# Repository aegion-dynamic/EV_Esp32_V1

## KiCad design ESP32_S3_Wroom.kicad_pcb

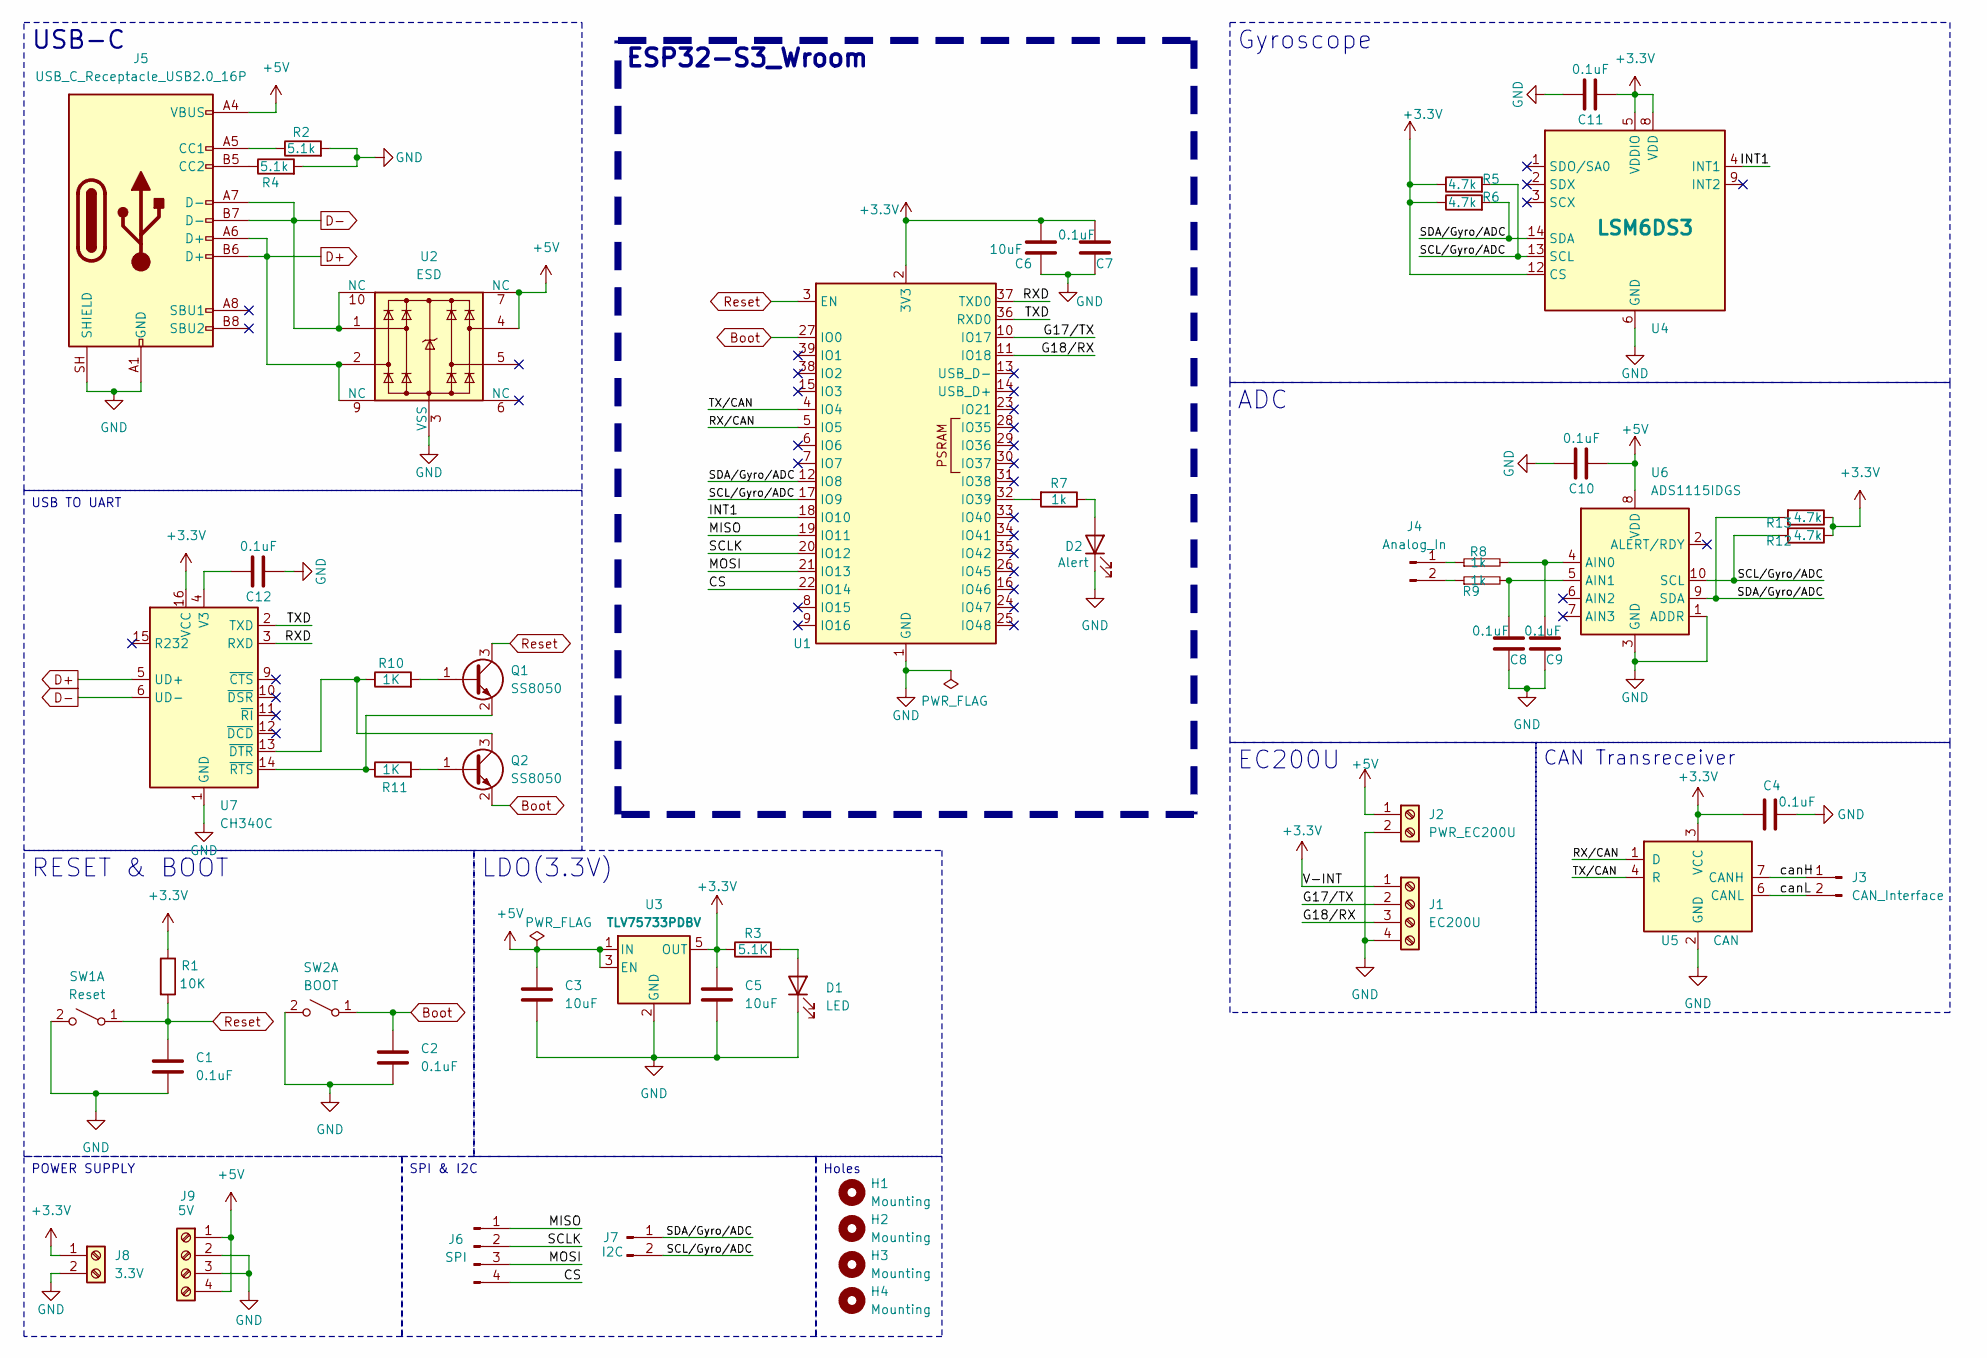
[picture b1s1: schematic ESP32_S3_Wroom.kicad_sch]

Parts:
C1, C2, C4, C7, C8, C9, C10, C11, C12: 0.1uF; C_0603_1608Metric_Pad1.08x0.95mm_HandSolder
C3, C5, C6: 10uF; C_0805_2012Metric
D1: LED; LED_0603_1608Metric
D2: Alert; LED_0603_1608Metric
H1, H2, H3, H4: Mounting; MountingHole_3.2mm_M3_ISO14580
J1: EC200U; TerminalBlock_Xinya_XY308-2.54-4P_1x04_P2.54mm_Horizontal
J2: PWR_EC200U; TerminalBlock_Xinya_XY308-2.54-2P_1x02_P2.54mm_Horizontal
J3: CAN_Interface; JST_EH_B2B-EH-A_1x02_P2.50mm_Vertical
J4: Analog_In; PinHeader_1x02_P2.54mm_Vertical
J5: USB_C_Receptacle_USB2.0_16P; USB_C_Receptacle_GCT_USB4105-xx-A_16P_TopMnt_Horizontal
J6: SPI; PinHeader_1x04_P2.54mm_Vertical
J7: I2C; PinHeader_1x02_P2.54mm_Vertical
J8: 3.3V; TerminalBlock_Xinya_XY308-2.54-2P_1x02_P2.54mm_Horizontal
J9: 5V; TerminalBlock_Xinya_XY308-2.54-4P_1x04_P2.54mm_Horizontal
Q1, Q2: SS8050; SOT-23
R1: 10K; R_0805_2012Metric
R2, R4: 5.1k; R_0805_2012Metric
R3: 5.1K; R_0805_2012Metric
R5, R6, R12, R13: 4.7k; R_0603_1608Metric_Pad0.98x0.95mm_HandSolder
R7, R8, R9: 1k; R_0603_1608Metric_Pad0.98x0.95mm_HandSolder
R10, R11: 1K; R_0603_1608Metric_Pad0.98x0.95mm_HandSolder
SW1: Reset; SW_SPST_TL3305A
SW2: BOOT; SW_SPST_TL3305A
U1: ESP32-S3-WROOM-1
U2: ESD; Diodes_UDFN-10_1x2.5mm_P0.5mm
U3: TLV75733PDBV; SOT-23-5
U4: LSM6DS3; LGA-14_3x2.5mm_P0.5mm_LayoutBorder3x4y
U5: CAN; SOIC-8_3.9x4.9mm_P1.27mm
U6: ADS1115IDGS; TSSOP-10_3x3mm_P0.5mm
U7: CH340C; SOIC-16_3.9x9.9mm_P1.27mm

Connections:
+3.3V: C4.1, C5.1, C6.1, C7.1, C11.2, J1.1, J8.1, R1.1, R3.1, R5.1, R6.1, R12.1, R13.1, U1.2 (3V3), U3.5 (OUT), U4.5 (VDDIO), U4.8 (VDD), U4.12 (CS), U5.3 (VCC), U7.16 (VCC)
+5V: C3.1, C10.2, J2.1, J5.A4 (VBUS), J5.A9 (VBUS), J5.B4 (VBUS), J5.B9 (VBUS), J9.1, J9.4, U2.4, U2.7 (NC), U3.1 (IN), U3.3 (EN), U6.8 (VDD)
/CS: J6.4, U1.22 (IO14)
/G17/TX: J1.2, U1.10 (IO17)
/G18/RX: J1.3, U1.11 (IO18)
/INT1: U1.18 (IO10), U4.4 (INT1)
/MISO: J6.1, U1.19 (IO11)
/MOSI: J6.3, U1.21 (IO13)
/RXD: U1.37 (TXD0), U7.3 (RXD)
/RX/CAN: U1.5 (IO5), U5.1 (D)
/SCLK: J6.2, U1.20 (IO12)
/SCL/Gyro/ADC: J7.2, R5.2, R12.2, U1.17 (IO9), U4.13 (SCL), U6.10 (SCL)
/SDA/Gyro/ADC: J7.1, R6.2, R13.2, U1.12 (IO8), U4.14 (SDA), U6.9 (SDA)
/TXD: U1.36 (RXD0), U7.2 (TXD)
/TX/CAN: U1.4 (IO4), U5.4 (R)
/canH: J3.1, U5.7 (CANH)
/canL: J3.2, U5.6 (CANL)
Boot: C2.1, Q2.2 (E), SW2.1 (A), U1.27 (IO0)
D+: J5.A6 (D+), J5.B6 (D+), U2.2, U2.9 (NC), U7.5 (UD+)
D-: J5.A7 (D-), J5.B7 (D-), U2.1, U2.10 (NC), U7.6 (UD-)
GND: C1.2, C2.2, C3.2, C4.2, C5.2, C6.2, C7.2, C8.2, C9.2, C10.1, C11.1, C12.2, D1.1 (K), D2.1 (K), J1.4, J2.2, J5.A1 (GND), J5.A12 (GND), J5.B1 (GND), J5.B12 (GND), J5.SH (SHIELD), J8.2, J9.2, J9.3, R2.2, R4.2, SW1.2 (B), SW2.2 (B), U1.1 (GND), U1.40 (GND), U1.41 (GND), U2.3 (VSS), U2.8 (VSS), U3.2 (GND), U4.6 (GND), U4.7 (GND), U5.2 (GND), U6.1 (ADDR), U6.3 (GND), U7.1 (GND)
unnamed: D1.2 (A), R3.2
unnamed: D2.2 (A), R7.1
unnamed: J4.1, R8.1
unnamed: J4.2, R9.1
unnamed: J5.A5 (CC1), R2.1
unnamed: J5.B5 (CC2), R4.1
unnamed: Q1.1 (B), R10.2
unnamed: Q1.2 (E), R11.1, U7.14 (~RTS)
unnamed: Q2.1 (B), R11.2
unnamed: Q2.3 (C), R10.1, U7.13 (~DTR)
unnamed: R7.2, U1.32 (IO39)
unnamed: C9.1, R8.2, U6.4 (AIN0)
unnamed: C8.1, R9.2, U6.5 (AIN1)
unnamed: C12.1, U7.4 (V3)
Reset: C1.1, Q1.3 (C), R1.2, SW1.1 (A), U1.3 (EN)

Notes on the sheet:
USB-C
EC200U
USB TO UART
RESET & BOOT
Gyroscope
LDO(3.3V)
CAN Transreceiver
POWER SUPPLY
ESP32-S3_Wroom
SPI & I2C
Holes
ADC

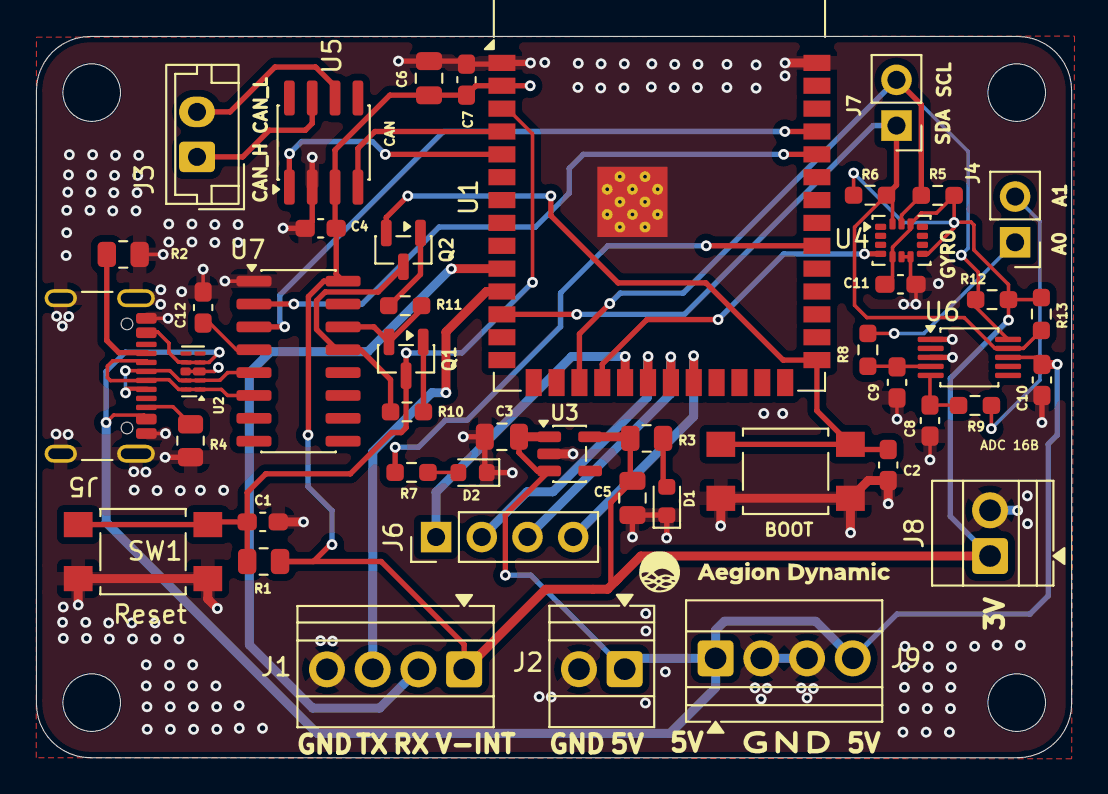
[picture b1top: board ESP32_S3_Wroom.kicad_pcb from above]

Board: 2 copper layers, 57.5 x 40.1 mm, 51 parts (0 on the bottom side), 36 nets.
